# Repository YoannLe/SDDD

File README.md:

# SDDD

This is a simple direct drive desulfaltor for lead acid battery 12V blocs

You can find schematic, PCB and Gerber files to build a direct drive desulfaltor circuit. This circuit pulses a high current from 30 to 100A at about 2kHz into the battery block to break lead sulfate cristals.

The pulse board drives MOSFET with impulsions from 555 and discharges the capacitor bank into the battery bloc. The capacitor bank is load at 30V DC through a 10W resistor to limit charge current, different values of resistors can be selected to adapt the power of desulfator to the sulfated battery.
Capacitor bank is made with very low ESR electrolytic caps in parallel, the capacity is about 30 mf, in my case:  30 x 1000µf 63V ESR=43mΩ PANASONIC EEUFC1J102U

# SDDD Pulse Board

The main board is the pulse generator board, it drives Mosfets:

Frequency and pulses timming can be calculated as described by Tucsonshooter:

>Pulse width = 1.1 * R6 * C8         (capacitance in farads,  .01 mF = .00000001 farads). 
>Example: 1.1 * 3000*.00000001 = .000033 seconds or 33 microseconds.
>
>Frequency = (R2 * Vcc - .65(R2+R3)) / (.333 * Vcc * R4(R2+R3) * C6)
>In this case Vcc = 12V
>And remember capacitance is in farads. Watch the parentheses (X +Y) 
>
>Example: (3000 * 12 - .65( 3000 + 22500))/ (.333 * 12 * 10000(3000 + 22500) * .00000001 =    (36000-16575) / 10.1898     = 1906 Hertz
>
>The frequency formula looks complicated but it is just adding and multiplying in the right order. If you break the formula down and put >it in Excell it will be much easier.
>
>Thermistors 
>  Remember - a 3K NTC thermistor will read 3K at room temperature (25 deg. C.). It will read about 1.5K at 45 deg.C.

A 3k NTC could be used for R2 to reduce frequency from 2kHz at 24° to 250Hz at 45°, this reduce the average power in the MOSFET and protects it from overheat on good batteries with low internal resistances. This slows frequency when the sulfated battery recovers its capacity and low internal resistance.

This board can be cut in fonction blocs when opening jumpers, this is usefull for testing and try others configurations. An optocoupler connected to Vcc and PAD1 can be use to stop pulses from an MCU or arduino. Stop pulsing can be usefull to control battery voltage or in case of battery overheating. 

# Capacitor bank and power supply

# Assembly

# Tests

# Results on 12V 90Ah AGM Battery

First if the battery is old and have been over charged, open the sealed battery to check electrolyte level and refill with demineralized water. The level must be just above the glass mast.

#References

Forum Direct Drive Desulfator Design:

http://leadacidbatterydesulfation.yuku.com/topic/1162/Direct%E2%88%92Drive%E2%88%92Desulfator%E2%88%92Design
http://leadacidbatterydesulfation.yuku.com/topic/1246/Simple-Direct-Drive-Desulfator-PCB-thread
http://www.courtiestown.co.uk/fileuploader/download/download/?d=0&file=custom%2Fupload%2FFile-1368475803.pdf

Evolutions:

http://www.brettcave.net/howto/circuits/Battery_LeadAcidDesulfator-DirectDrive-Type2.pdf
http://www.brettcave.net/howto/circuits/Battery_LeadAcidDesulfator-DirectDrive-Type3.pdf

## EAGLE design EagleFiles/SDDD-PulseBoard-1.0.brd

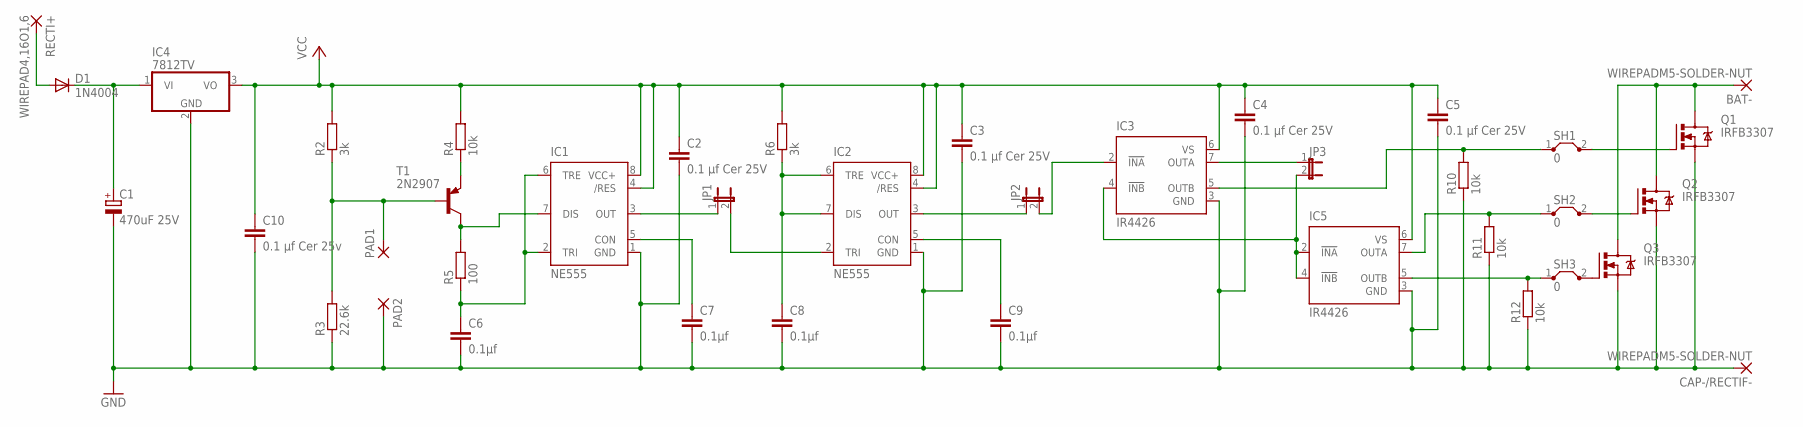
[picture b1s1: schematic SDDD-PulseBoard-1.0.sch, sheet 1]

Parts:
BAT-: WIREPADM5-SOLDER-NUT; M5-SOLDER-NUT
C1: 470uF 25V; E5-8,5
C2, C3, C4, C5: 0.1 µf Cer 25V; C050-025X075
C6, C7, C8, C9: 0.1µf; C050-025X075
C10: 0.1 µf Cer 25v; C050-025X075
CAP-/RECTIF-: WIREPADM5-SOLDER-NUT; M5-SOLDER-NUT
D1: 1N4004; DO41-10
IC1, IC2: NE555; DIL-08
IC3, IC5: IR4426; DIL08
IC4: 7812TV; TO220V
JP1, JP2, JP3: JP1E; JP1
PAD1, PAD2: 2,15/1,0
Q1, Q2, Q3: IRFB3307; TO220BV
R2, R6: 3k; 0207/10
R3: 22.6k; 0207/10
R4, R10, R11, R12: 10k; 0207/10
R5: 100; 0207/10
RECTI+: WIREPAD4,16O1,6; 4,16O1,6
SH1, SH2, SH3: 0; 30
T1: 2N2907; TO92-CBE

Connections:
GND: C1.-, C2.2, C3.2, C4.2, C5.2, C6.2, C7.2, C8.2, C9.2, C10.2, CAP-/RECTIF-.1, CAP-/RECTIF-.P$1, CAP-/RECTIF-.P$2, CAP-/RECTIF-.P$3, CAP-/RECTIF-.P$4, CAP-/RECTIF-.P$5, CAP-/RECTIF-.P$6, CAP-/RECTIF-.P$7, CAP-/RECTIF-.P$8, CAP-/RECTIF-.P$9, CAP-/RECTIF-.P$10, CAP-/RECTIF-.P$11, CAP-/RECTIF-.P$12, CAP-/RECTIF-.P$13, CAP-/RECTIF-.P$14, CAP-/RECTIF-.P$15, CAP-/RECTIF-.P$16, CAP-/RECTIF-.P$17, CAP-/RECTIF-.P$18, CAP-/RECTIF-.P$19, CAP-/RECTIF-.P$20, CAP-/RECTIF-.P$21, CAP-/RECTIF-.P$22, CAP-/RECTIF-.P$23, CAP-/RECTIF-.P$24, CAP-/RECTIF-.P$25, CAP-/RECTIF-.P$26, CAP-/RECTIF-.P$27, CAP-/RECTIF-.P$28, CAP-/RECTIF-.P$29, CAP-/RECTIF-.P$30, CAP-/RECTIF-.P$31, CAP-/RECTIF-.P$32, CAP-/RECTIF-.P$33, CAP-/RECTIF-.P$34, CAP-/RECTIF-.P$35, CAP-/RECTIF-.P$36, CAP-/RECTIF-.P$37, CAP-/RECTIF-.P$38, CAP-/RECTIF-.P$39, CAP-/RECTIF-.P$40, CAP-/RECTIF-.P$41, CAP-/RECTIF-.P$42, CAP-/RECTIF-.P$43, CAP-/RECTIF-.P$44, CAP-/RECTIF-.P$45, CAP-/RECTIF-.P$46, CAP-/RECTIF-.P$47, CAP-/RECTIF-.P$48, CAP-/RECTIF-.P$49, CAP-/RECTIF-.P$50, CAP-/RECTIF-.P$51, CAP-/RECTIF-.P$52, CAP-/RECTIF-.P$53, CAP-/RECTIF-.P$54, CAP-/RECTIF-.P$55, CAP-/RECTIF-.P$56, CAP-/RECTIF-.P$57, CAP-/RECTIF-.P$58, CAP-/RECTIF-.P$59, CAP-/RECTIF-.P$60, CAP-/RECTIF-.P$61, CAP-/RECTIF-.P$62, CAP-/RECTIF-.P$63, CAP-/RECTIF-.P$64, CAP-/RECTIF-.P$65, CAP-/RECTIF-.P$66, CAP-/RECTIF-.P$67, CAP-/RECTIF-.P$68, CAP-/RECTIF-.P$69, CAP-/RECTIF-.P$70, CAP-/RECTIF-.P$71, CAP-/RECTIF-.P$72, CAP-/RECTIF-.P$73, CAP-/RECTIF-.P$74, CAP-/RECTIF-.P$75, CAP-/RECTIF-.P$76, CAP-/RECTIF-.P$77, CAP-/RECTIF-.P$78, CAP-/RECTIF-.P$79, CAP-/RECTIF-.P$80, IC1.1 (GND), IC2.1 (GND), IC3.3 (GND), IC4.2 (GND), IC5.3 (GND), PAD2.1, Q1.S, Q2.S, Q3.S, R3.1, R10.1, R11.1, R12.1
unnamed: IC3.5 (OUTB), R10.2, SH1.1
unnamed: PAD1.1, R2.1, R3.2, T1.B
unnamed: C6.1, IC1.2 (TRI), IC1.6 (TRE), R5.1
unnamed: Q1.G, SH1.2
unnamed: BAT-.1, BAT-.P$1, BAT-.P$2, BAT-.P$3, BAT-.P$4, BAT-.P$5, BAT-.P$6, BAT-.P$7, BAT-.P$8, BAT-.P$9, BAT-.P$10, BAT-.P$11, BAT-.P$12, BAT-.P$13, BAT-.P$14, BAT-.P$15, BAT-.P$16, BAT-.P$17, BAT-.P$18, BAT-.P$19, BAT-.P$20, BAT-.P$21, BAT-.P$22, BAT-.P$23, BAT-.P$24, BAT-.P$25, BAT-.P$26, BAT-.P$27, BAT-.P$28, BAT-.P$29, BAT-.P$30, BAT-.P$31, BAT-.P$32, BAT-.P$33, BAT-.P$34, BAT-.P$35, BAT-.P$36, BAT-.P$37, BAT-.P$38, BAT-.P$39, BAT-.P$40, BAT-.P$41, BAT-.P$42, BAT-.P$43, BAT-.P$44, BAT-.P$45, BAT-.P$46, BAT-.P$47, BAT-.P$48, BAT-.P$49, BAT-.P$50, BAT-.P$51, BAT-.P$52, BAT-.P$53, BAT-.P$54, BAT-.P$55, BAT-.P$56, BAT-.P$57, BAT-.P$58, BAT-.P$59, BAT-.P$60, BAT-.P$61, BAT-.P$62, BAT-.P$63, BAT-.P$64, BAT-.P$65, BAT-.P$66, BAT-.P$67, BAT-.P$68, BAT-.P$69, BAT-.P$70, BAT-.P$71, BAT-.P$72, BAT-.P$73, BAT-.P$74, BAT-.P$75, BAT-.P$76, BAT-.P$77, BAT-.P$78, BAT-.P$79, BAT-.P$80, Q1.D, Q2.D, Q3.D
unnamed: IC5.7 (OUTA), R11.2, SH2.1
unnamed: Q2.G, SH2.2
unnamed: IC5.5 (OUTB), R12.2, SH3.1
unnamed: R4.1, T1.E
unnamed: IC1.7 (DIS), R5.2, T1.C
unnamed: Q3.G, SH3.2
unnamed: C7.1, IC1.5 (CON)
unnamed: C8.1, IC2.6 (TRE), IC2.7 (DIS), R6.1
unnamed: IC1.3 (OUT), JP1.1
unnamed: IC2.2 (TRI), JP1.2
unnamed: IC2.3 (OUT), JP2.1
unnamed: IC3.2 (!INA), JP2.2
unnamed: IC3.7 (OUTA), JP3.1
unnamed: IC3.4 (!INB), IC5.2 (!INA), IC5.4 (!INB), JP3.2
unnamed: C1.+, D1.C, IC4.1 (VI)
unnamed: C9.1, IC2.5 (CON)
unnamed: D1.A, RECTI+.1
VCC: C2.1, C3.1, C4.1, C5.1, C10.1, IC1.4 (/RES), IC1.8 (VCC+), IC2.4 (/RES), IC2.8 (VCC+), IC3.6 (VS), IC4.3 (VO), IC5.6 (VS), R2.2, R4.2, R6.2

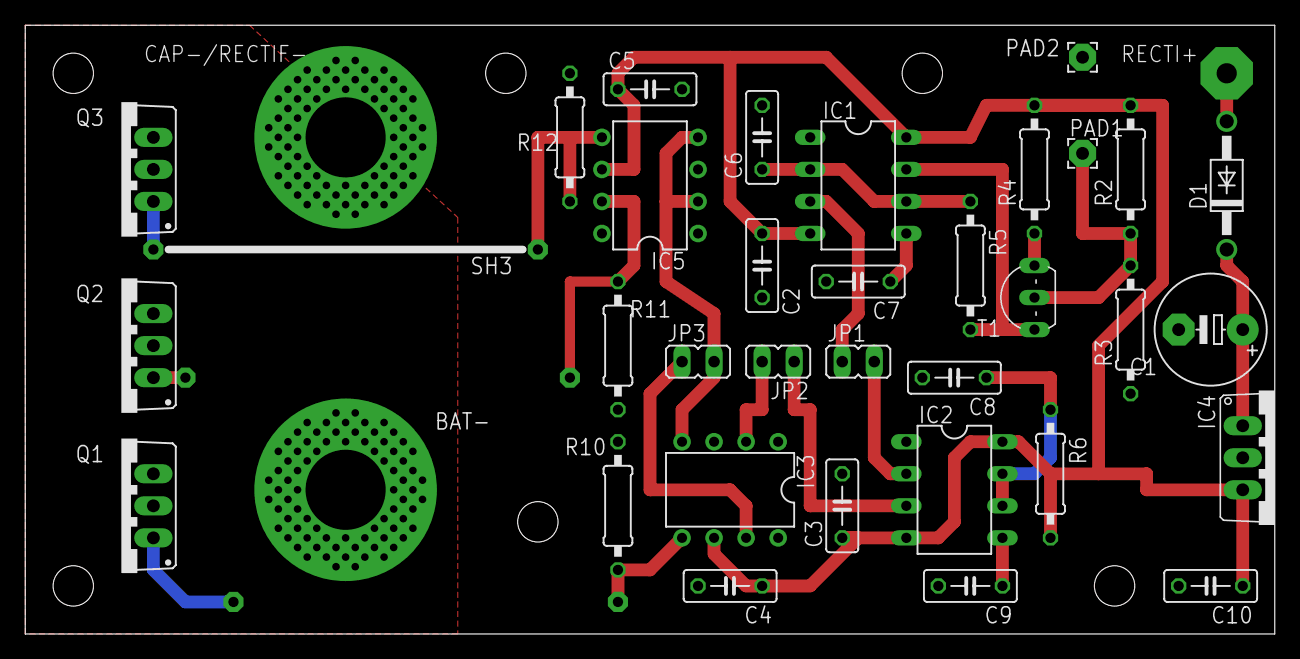
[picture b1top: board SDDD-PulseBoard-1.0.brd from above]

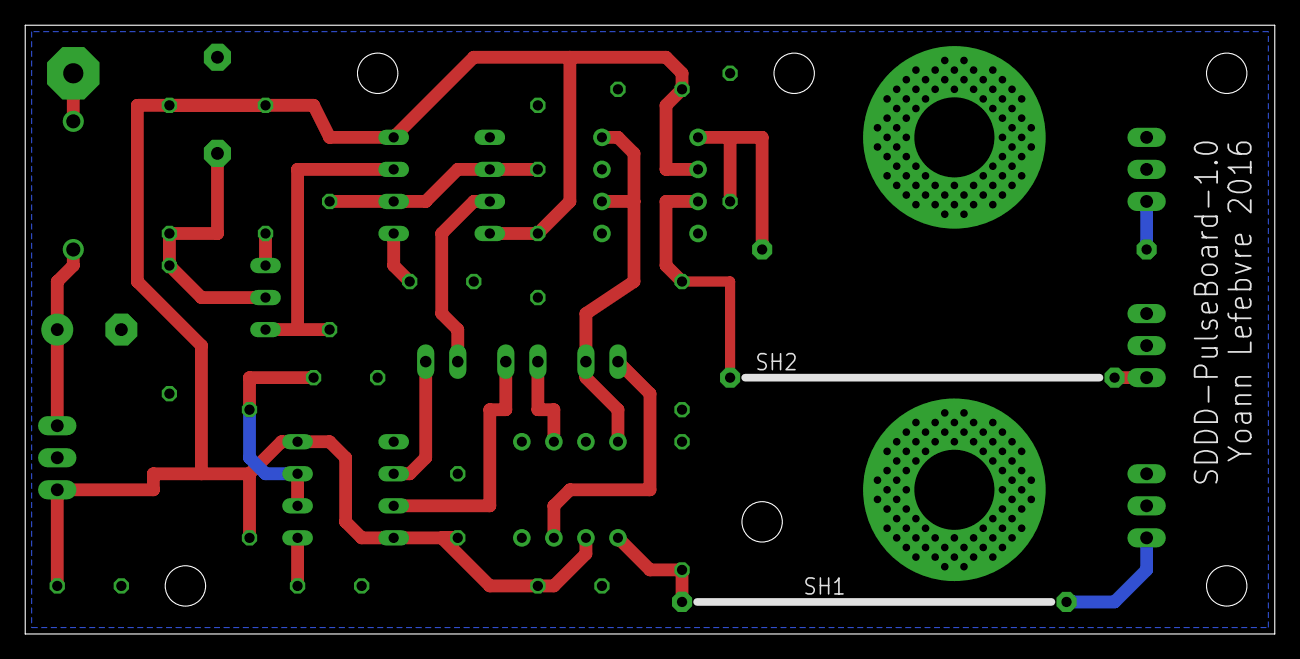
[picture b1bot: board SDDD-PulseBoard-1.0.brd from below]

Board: 2 copper layers, 99.1 x 48.3 mm, 39 parts (2 on the bottom side), 24 nets.

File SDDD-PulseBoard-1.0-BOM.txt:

Partlist exported from D:/ylefebvre/Bureau/SDDD/SDDD-Eagle/SDDD-PulseBoard-1.0.sch at 29/09/2016 17:54

Part         Value                Device                Package       Description                          MF                          MPN       OC_FARNELL OC_NEWARK
BAT-         WIREPADM5-SOLDER-NUT WIREPADM5-SOLDER-NUT  M5-SOLDER-NUT Wire PAD connect wire on PCB                                                                   
C1           470uF 25V            CPOL-EUE5-8.5         E5-8,5        POLARIZED CAPACITOR, European symbol                                                           
C2           0.1 µf Cer 25V       C-EU050-025X075       C050-025X075  CAPACITOR, European symbol                                                                     
C3           0.1 µf Cer 25V       C-EU050-025X075       C050-025X075  CAPACITOR, European symbol                                                                     
C4           0.1 µf Cer 25V       C-EU050-025X075       C050-025X075  CAPACITOR, European symbol                                                                     
C5           0.1 µf Cer 25V       C-EU050-025X075       C050-025X075  CAPACITOR, European symbol                                                                     
C6           0.1µf                C-EU050-025X075       C050-025X075  CAPACITOR, European symbol                                                                     
C7           0.1µf                C-EU050-025X075       C050-025X075  CAPACITOR, European symbol                                                                     
C8           0.1µf                C-EU050-025X075       C050-025X075  CAPACITOR, European symbol                                                                     
C9           0.1µf                C-EU050-025X075       C050-025X075  CAPACITOR, European symbol                                                                     
C10          0.1 µf Cer 25v       C-EU050-025X075       C050-025X075  CAPACITOR, European symbol                                                                     
CAP-/RECTIF- WIREPADM5-SOLDER-NUT WIREPADM5-SOLDER-NUT  M5-SOLDER-NUT Wire PAD connect wire on PCB                                                                   
D1           1N4004               1N4004                DO41-10       DIODE                                                                                          
IC1          NE555                NE555                 DIL-08        General purpose bipolar Timer        Arrow Electronics           NE555N    1467742    89K1486  
IC2          NE555                NE555                 DIL-08        General purpose bipolar Timer        Arrow Electronics           NE555N    1467742    89K1486  
IC3          IR4426               IR4426                DIL08         DUAL LOW SIDE DRIVER                 INTERNATIONAL RECTIFIER(IR) IR4426PBF 1023265    19K8460  
IC4          7812TV               7812TV                TO220V        Positive VOLTAGE REGULATOR                                                                     
IC5          IR4426               IR4426                DIL08         DUAL LOW SIDE DRIVER                 INTERNATIONAL RECTIFIER(IR) IR4426PBF 1023265    19K8460  
JP1                               JP1E                  JP1           JUMPER                                                                                         
JP2                               JP1E                  JP1           JUMPER                                                                                         
JP3                               JP1E                  JP1           JUMPER                                                                                         
PAD1                              2,15/1,0              2,15/1,0      THROUGH-HOLE PAD                                                                               
PAD2                              2,15/1,0              2,15/1,0      THROUGH-HOLE PAD                                                                               
Q1           IRFB3307             IRF540                TO220BV       HEXFET Power MOSFET                                                                            
Q2           IRFB3307             IRF540                TO220BV       HEXFET Power MOSFET                                                                            
Q3           IRFB3307             IRF540                TO220BV       HEXFET Power MOSFET                                                                            
R2           3k                   R-EU_0207/10          0207/10       RESISTOR, European symbol                                                                      
R3           22.6k                R-EU_0207/10          0207/10       RESISTOR, European symbol                                                                      
R4           10k                  R-EU_0207/10          0207/10       RESISTOR, European symbol                                                                      
R5           100                  R-EU_0207/10          0207/10       RESISTOR, European symbol                                                                      
R6           3k                   R-EU_0207/10          0207/10       RESISTOR, European symbol                                                                      
R10          10k                  R-EU_0207/10          0207/10       RESISTOR, European symbol                                                                      
R11          10k                  R-EU_0207/10          0207/10       RESISTOR, European symbol                                                                      
R12          10k                  R-EU_0207/10          0207/10       RESISTOR, European symbol                                                                      
RECTI+       WIREPAD4,16O1,6      WIREPAD4,16O1,6       4,16O1,6      Wire PAD connect wire on PCB                                                                   
SH1          0                    J30MM                 30            Bridge                                                                                         
SH2          0                    J30MM                 30            Bridge                                                                                         
SH3          0                    J30MM                 30            Bridge                                                                                         
T1           2N2907               MPS2907A-PNP-TO92-CBE TO92-CBE      PNP Transistror
